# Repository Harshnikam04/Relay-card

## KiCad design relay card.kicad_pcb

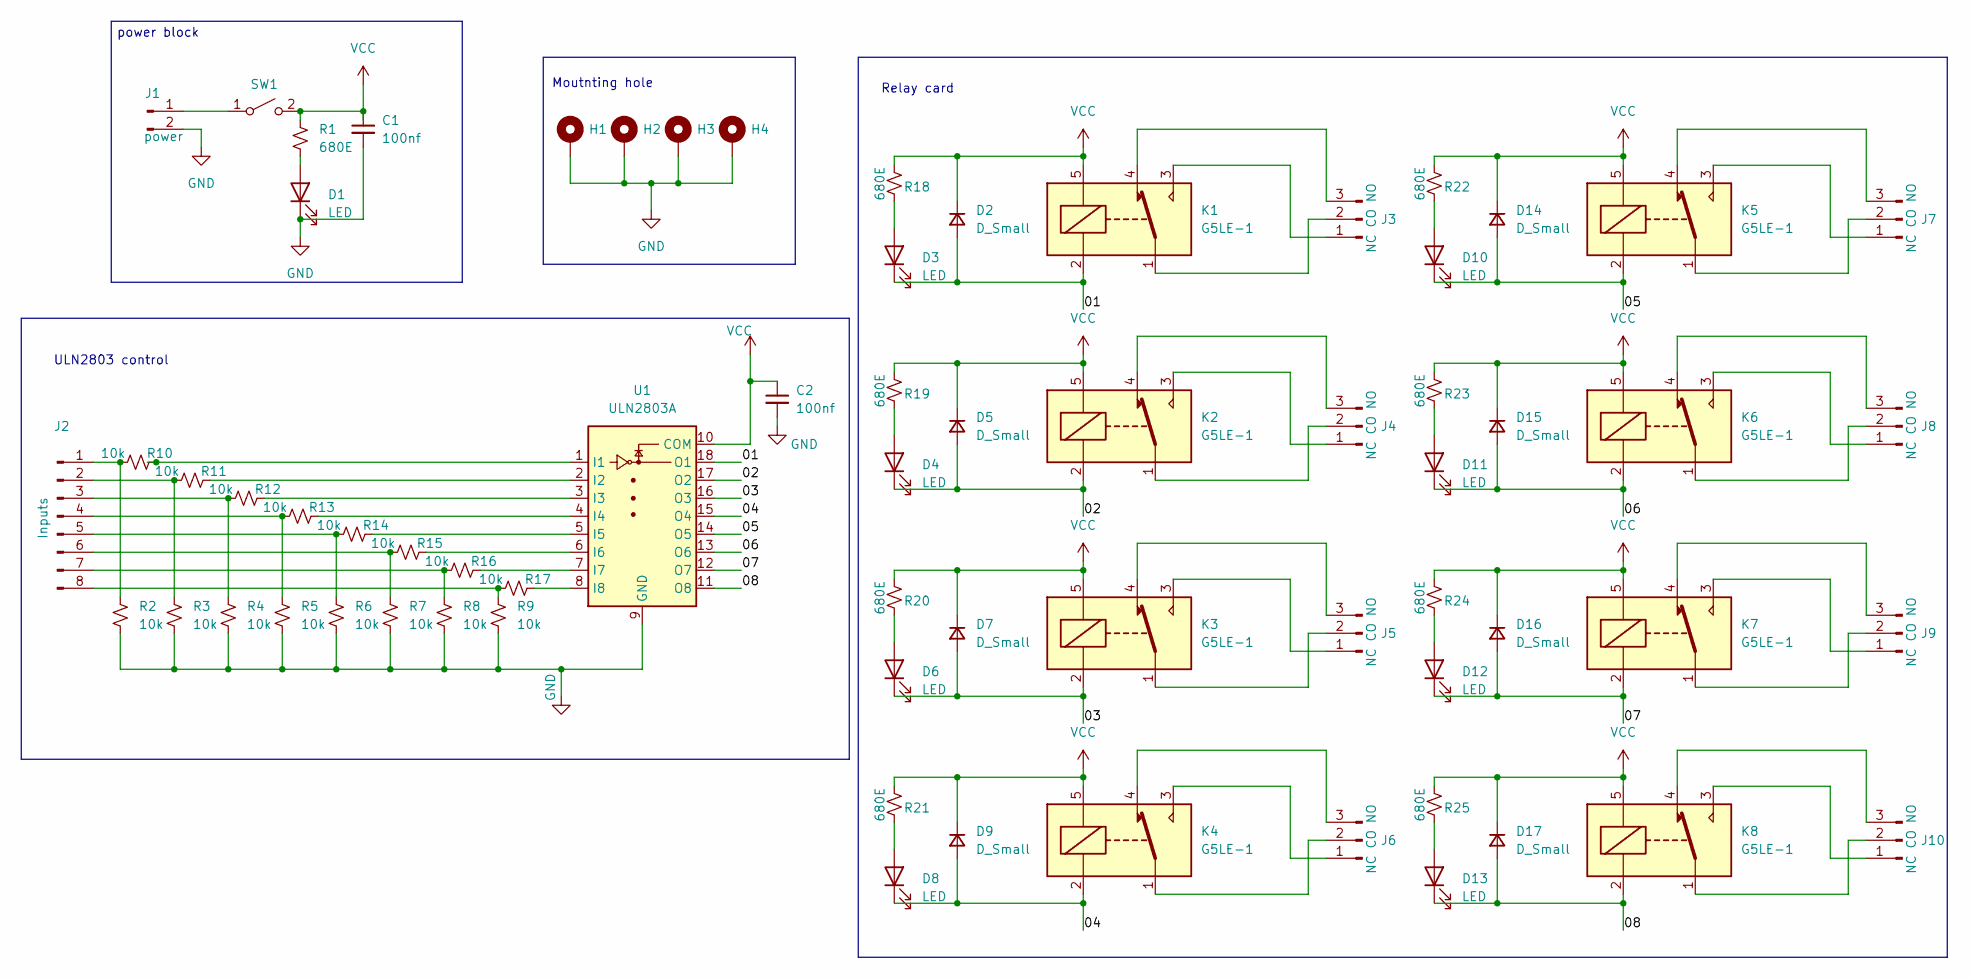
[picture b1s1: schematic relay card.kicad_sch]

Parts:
C1, C2: 100nf; C_0805_2012Metric
D1, D3, D4, D6, D8, D10, D11, D12, D13: LED; LED_1206_3216Metric
D2, D5, D7, D9, D14, D15, D16, D17: D_Small; D_1206_3216Metric
H1, H2, H3, H4: MountingHole_Pad; MountingHole_2.5mm_Pad_Via
J1: power; JST_NV_B02P-NV_1x02_P5.00mm_Vertical
J2: Inputs; PinHeader_1x08_P2.54mm_Vertical
J3, J4, J5, J6, J7, J8, J9, J10: NC CO NO; JST_NV_B03P-NV_1x03_P5.00mm_Vertical
K1, K2, K3, K4, K5, K6, K7, K8: G5LE-1; Relay_SPDT_Omron-G5LE-1
R1, R18, R19, R20, R21, R22, R23, R24, R25: 680E; R_0805_2012Metric
R2, R3, R4, R5, R6, R7, R8, R9, R10, R11, R12, R13, R14, R15, R16, R17: 10k; R_0805_2012Metric
SW1: SW_SPST; SW_DIP_SPSTx01_Slide_6.7x4.1mm_W8.61mm_P2.54mm_LowProfile
U1: ULN2803A; DIP-18_W7.62mm_LongPads

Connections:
/01: D2.2 (A), D3.1 (K), K1.2, U1.18 (O1)
/02: D4.1 (K), D5.2 (A), K2.2, U1.17 (O2)
/03: D6.1 (K), D7.2 (A), K3.2, U1.16 (O3)
/04: D8.1 (K), D9.2 (A), K4.2, U1.15 (O4)
/05: D10.1 (K), D14.2 (A), K5.2, U1.14 (O5)
/06: D11.1 (K), D15.2 (A), K6.2, U1.13 (O6)
/07: D12.1 (K), D16.2 (A), K7.2, U1.12 (O7)
/08: D13.1 (K), D17.2 (A), K8.2, U1.11 (O8)
GND: C1.2, C2.2, D1.1 (K), H1.1, H2.1, H3.1, H4.1, J1.2, R2.2, R3.2, R4.2, R5.2, R6.2, R7.2, R8.2, R9.2, U1.9 (GND)
unnamed: D1.2 (A), R1.2
unnamed: D3.2 (A), R18.2
unnamed: D4.2 (A), R19.2
unnamed: D6.2 (A), R20.2
unnamed: D8.2 (A), R21.2
unnamed: D10.2 (A), R22.2
unnamed: D11.2 (A), R23.2
unnamed: D12.2 (A), R24.2
unnamed: D13.2 (A), R25.2
unnamed: J1.1, SW1.1 (A)
unnamed: J2.1, R2.1, R10.1
unnamed: J2.2, R3.1, R11.1
unnamed: J2.3, R4.1, R12.1
unnamed: J2.4, R5.1, R13.1
unnamed: J2.5, R6.1, R14.1
unnamed: J2.6, R7.1, R15.1
unnamed: J2.7, R8.1, R16.1
unnamed: J2.8, R9.1, R17.1
unnamed: J3.1, K1.3
unnamed: J3.2, K1.1
unnamed: J3.3, K1.4
unnamed: J4.1, K2.3
unnamed: J4.2, K2.1
unnamed: J4.3, K2.4
unnamed: J5.1, K3.3
unnamed: J5.2, K3.1
unnamed: J5.3, K3.4
unnamed: J6.1, K4.3
unnamed: J6.2, K4.1
unnamed: J6.3, K4.4
unnamed: J7.1, K5.3
unnamed: J7.2, K5.1
unnamed: J7.3, K5.4
unnamed: J8.1, K6.3
unnamed: J8.2, K6.1
unnamed: J8.3, K6.4
unnamed: J9.1, K7.3
unnamed: J9.2, K7.1
unnamed: J9.3, K7.4
unnamed: J10.1, K8.3
unnamed: J10.2, K8.1
unnamed: J10.3, K8.4
unnamed: R10.2, U1.1 (I1)
unnamed: R11.2, U1.2 (I2)
unnamed: R12.2, U1.3 (I3)
unnamed: R13.2, U1.4 (I4)
unnamed: R14.2, U1.5 (I5)
unnamed: R15.2, U1.6 (I6)
unnamed: R16.2, U1.7 (I7)
unnamed: R17.2, U1.8 (I8)
VCC: C1.1, C2.1, D2.1 (K), D5.1 (K), D7.1 (K), D9.1 (K), D14.1 (K), D15.1 (K), D16.1 (K), D17.1 (K), K1.5, K2.5, K3.5, K4.5, K5.5, K6.5, K7.5, K8.5, R1.1, R18.1, R19.1, R20.1, R21.1, R22.1, R23.1, R24.1, R25.1, SW1.2 (B), U1.10 (COM)

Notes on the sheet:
Relay card
Moutnting hole
power block
ULN2803 control

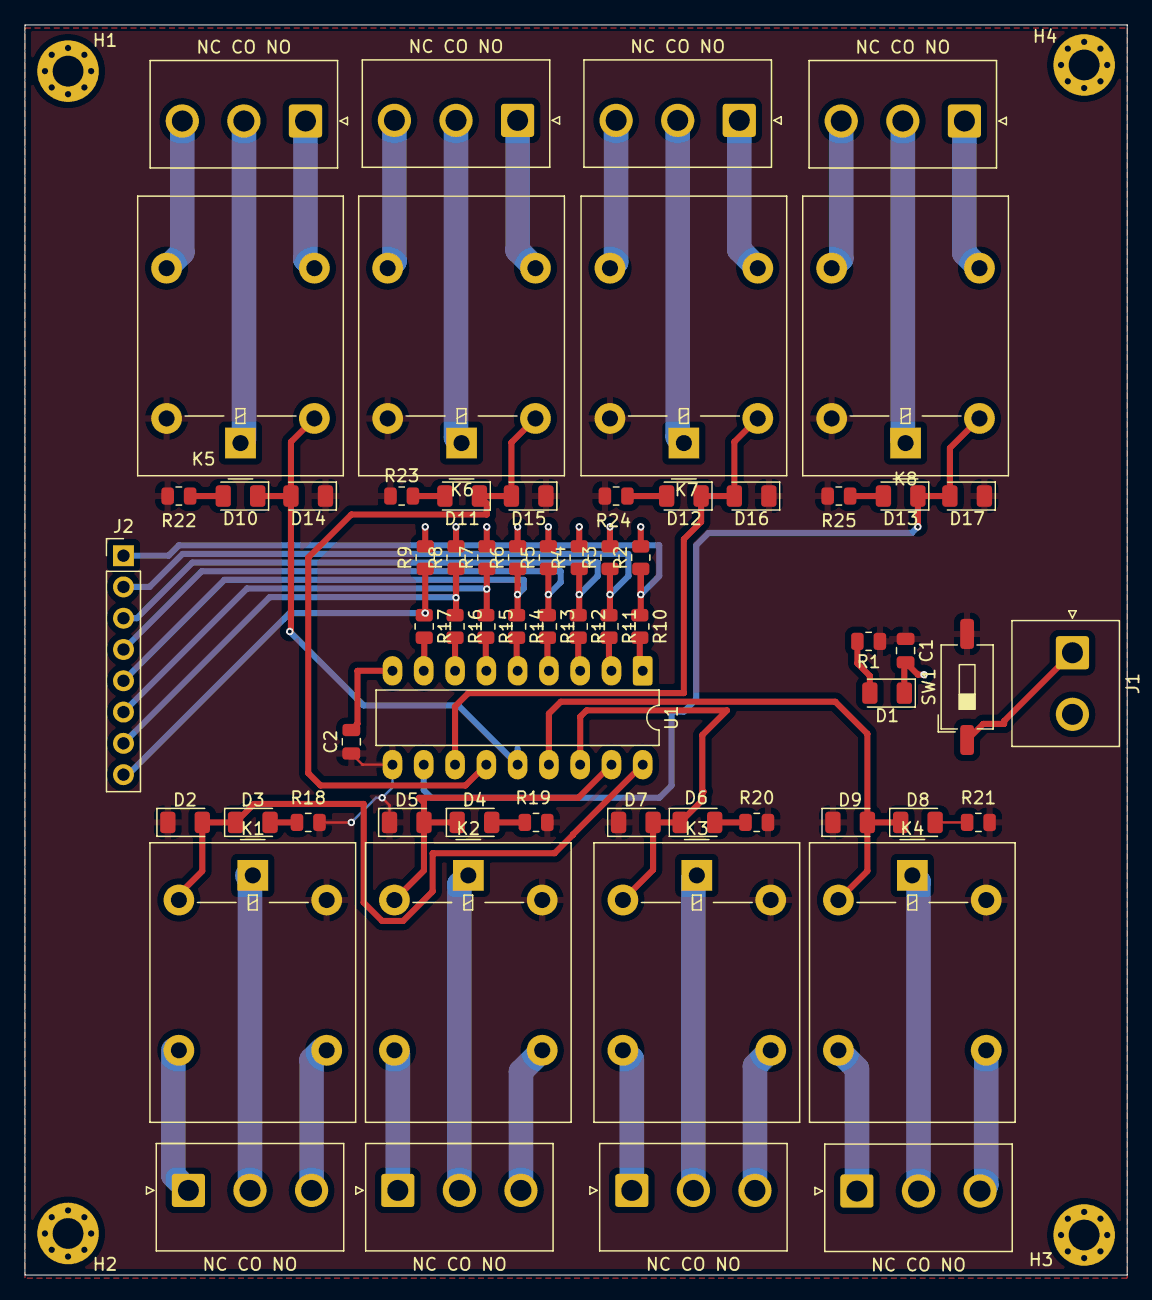
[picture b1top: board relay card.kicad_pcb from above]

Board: 2 copper layers, 89.5 x 101.5 mm, 68 parts (0 on the bottom side), 60 nets.
